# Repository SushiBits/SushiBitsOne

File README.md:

# SushiBits One

ARM Cortex-M in Arduino form factor, and consumes very little power.

## Introduction & Goal

This is one of my "design challenges" to myself:

*   Arduino-compatible form factor,
*   Take an 48-pin STM32 microcontroller (since STM32F103CBT6 are that cheap,)
*   Bring all I/O pins out somewhere, be it the connectors, JTAG or USB,
*   No two pins can be shorted together,
*   Use only switch-mode power supply,
*   Two layer PCB only,
*   Single side load.

## Main components

*   STM32 microcontroller in LQFP-48 package. I have tested the following:
    *   STM32F072C8T6 (Cortex-M0 @48MHz)
    *   STM32F103CBT6 (Cortex-M3 @72MHz)
    *   STM32L151CCT6 (Cortex-M3 @32MHz, ULP)
    *   STM32F303CCT6 (Cortex-M4F @72MHz)
    *   STM32F373CCT6 (Cortex-M4F @72MHz)
*   WCH CH340B: USB to UART adapter.
*   TI TPS562200: VIN to 5V buck converter.
*   TI LM3671-3.3: 5V to 3.3V buck converter.

## License

This is [open source hardware](http://www.oshwa.org/), licensed under the
[3-clause BSD license](LICENSE.md).

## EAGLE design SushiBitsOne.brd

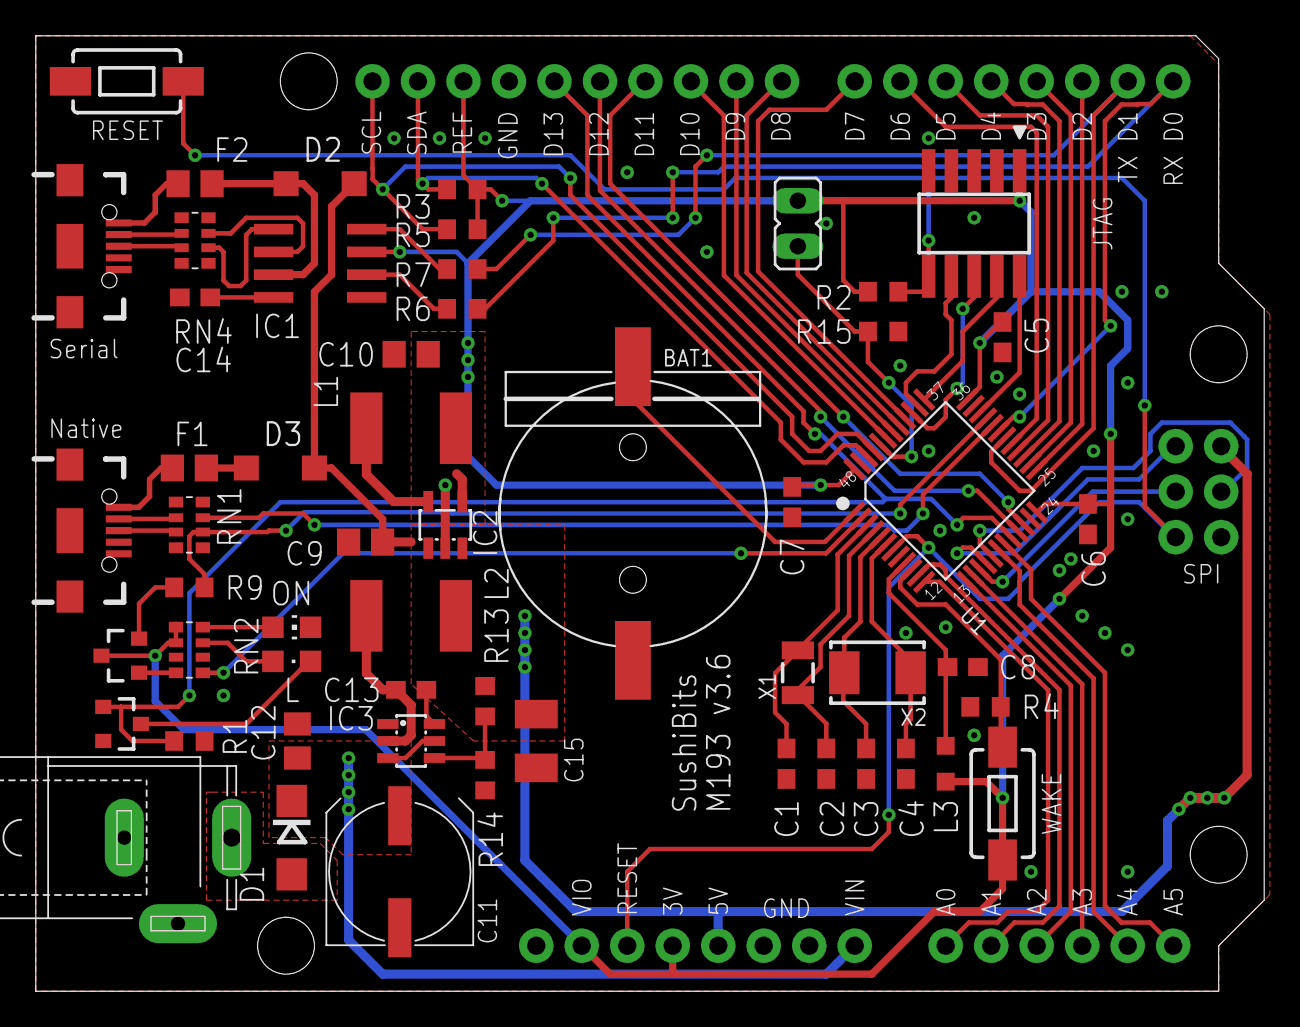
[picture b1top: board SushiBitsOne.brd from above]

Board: 2 copper layers, 68.6 x 53.3 mm, 56 parts (0 on the bottom side), 68 nets.

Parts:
BAT1: CR1220; BAT2P-SMD-16.4-CR1220
C1, C2: 3p; C0603
C3, C4: 22p; C0603
C5, C6, C7, C8, C13: 100n; C0603
C9, C10, C12: 10u; C0805
C11: 100u; UD-8X10_NICHICON
C14: 1u; C0603
C15: 220u; SMC_B
D1: SS34; DO214AC
D2, D3: SS14; SOD123
F1, F2: 500mA; R0805
IC1: HT42B534; SO8
IC2: LM3671-3.3DBV; SOT23-5L
IC3: TPS562200DBV; SOT23-6L
J1: ARDUINO_R3
J2: SPC4077
J3, J4: USB-B-MICRO-SMD
JP1: BOOT; JP1
L1: 2.2u; L5650M
L2: 4.7u; L5650M
L3: L2012C
LED1: Amber; CHIPLED_0805
LED2: Green; CHIP-LED0805
Q1: 2N7002; SOT23-3
Q2: MMBT2222A; SOT23-3
R1, R2, R4: 10k; R0603
R3, R5, R15: 4.7k; R0603
R6, R7: 510; R0603
R9: 1.5k; R0603
R13: 11k; R0603
R14: 2k; R0603
RN1, RN4: 22; EXB38V
RN2: 510; EXB38V
S1: RESET; TACTILE-SWITCH-1101NE
S2: WKUP; TACTILE-SWITCH-1101NE
U1: STM32F103CBT6-LQFP48; LQFP48-0.5-7X7MM
X1: 32768Hz; CRYSTAL-SMD-3.2X1.5MM
X2: 8MHz; CRYSTAL-SMD-5X3.2-2PAD
X3: JTAG; 1365-10

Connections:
+3V3: C5.1, C6.1, C7.1, C10.1, IC1.3, IC2.4, J1.3.3V, J1.AREF, J1.IOREF, JP1.1, L1.1, L3.1, Q2.3, R2.2, R3.2, R5.2, RN2.1, RN2.2, S2.2, U1.24, U1.36, U1.48, X3.1
+5V: C9.1, C15.+, D2.C, D3.C, IC2.1, IC2.3, J1.5V, J1.VCC, L2.1, R13.2
A0: J1.A0, U1.12
A1: J1.A1, U1.11
A2: J1.A2, U1.13
A3: J1.A3, U1.14
A4: J1.A4, U1.18
A5: J1.A5, U1.19
D2: J1.D2, U1.25
D3: J1.D3, U1.26
D4: J1.D4, U1.27
D5: J1.D5, U1.28
D6: J1.D6, U1.29
D7: J1.D7, U1.40
D8: J1.D8, U1.41
D9: J1.D9, U1.42
D10: J1.D10, U1.43
D11: J1.D11, U1.22
D12: J1.D12, U1.21
D13: J1.D13, Q1.1, R1.2, U1.20
D14: RN2.5, U1.2
GND: BAT1.-, C1.2, C2.2, C3.2, C4.2, C5.2, C6.2, C7.2, C8.2, C9.2, C10.2, C11.-, C12.2, C14.2, C15.-, IC1.1, IC2.2, IC3.1, J1.GND@1, J1.GND@2, J1.GND@3, J1.GND@4, J2.1, J2.2, J3.GND, J3.SHIELD1, J3.SHIELD2, J3.SHIELD3, J4.GND, J4.SHIELD1, J4.SHIELD2, J4.SHIELD3, LED2.C, Q1.2, R1.1, R4.1, R14.1, R15.1, S1.1, U1.8, U1.23, U1.35, U1.47, X3.3, X3.5, X3.9
HSEIN: C3.1, U1.5, X2.P$1
HSEOUT: C4.1, U1.6, X2.P$2
JTCK: U1.37, X3.4
JTDI: U1.38, X3.8
JTDO: U1.39, X3.6
JTMS: U1.34, X3.2
LSEIN: C1.1, U1.3, X1.P$1
LSEOUT: C2.1, U1.4, X1.P$2
MISO: J1.MISO, U1.16
MOSI: J1.MOSI, U1.17
unnamed: J4.D-, RN1.2
unnamed: J4.D+, RN1.3
unnamed: IC1.6, RN4.7
unnamed: IC1.5, RN4.6
unnamed: IC1.2, R6.1
unnamed: IC1.4, R7.1
unnamed: LED2.A, RN2.8
unnamed: LED1.C, Q1.3
unnamed: LED1.A, RN2.7
unnamed: IC2.5, L1.2
unnamed: D1.A, J2.3
unnamed: JP1.2, R15.2, U1.44
unnamed: D3.A, F1.2
unnamed: C13.1, IC3.2, L2.2
unnamed: C13.2, IC3.6
unnamed: D2.A, F2.2, IC1.7
unnamed: IC3.4, R13.1, R14.2
unnamed: Q2.2, R9.2
unnamed: Q2.1, RN2.4
unnamed: C8.1, L3.2, U1.9
unnamed: C14.1, IC1.8
unnamed: J3.D+, RN4.3
unnamed: J3.D-, RN4.2
unnamed: F2.1, J3.VBUS
RESET#: J1.RESET@1, J1.RESET@2, R2.1, S1.2, U1.7, X3.10
RXD: J1.D0, R6.2, U1.31
SCK: J1.SCK, U1.15
SCL: J1.SCL, R5.1, U1.45
SDA: J1.SDA, R3.1, U1.46
TXD: J1.D1, R7.2, U1.30
UD+: R9.1, RN1.6, U1.33
UD-: RN1.7, U1.32
VBAT: BAT1.+, U1.1
VBUS2: F1.1, J4.VBUS
VIN: C11.+, C12.1, D1.C, IC3.3, IC3.5, J1.VIN
WKUP: R4.2, S2.1, U1.10

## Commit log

2017-03-23 Initial Commit for completed project
2017-03-23 The ignore file missed the *.mil
2017-03-23 Added a README
2017-03-26 Fixing a typo in README
2017-08-19 Release: M193v3
2017-08-20 Updated copyright text in LICENSE
2017-11-02 Adjusting for the v4
2017-11-02 Ignoring a few EAGLE files
2017-11-02 Ignoring even more EAGLE files
2017-11-02 Implemented the USB microcontroller with USB-Serial and CMSIS-DAP.
2017-11-02 Ignoring release files
2017-11-02 Releasing M193v4
2017-11-02 Preparing v3.1 release.
2017-11-02 Missed a spot check on board silkscreen
2017-11-03 There is a net overlap.
2017-12-04 Relayout the board to accomodate component changes.
2017-12-04 Change up some footprints.
2017-12-20 Some manufacturability and cleanup work
2017-12-20 Squeezed the onboard debugger back in.
2017-12-20 Some details of the files are somehow changed?
2017-12-20 Adding the pin indicator back on DAP42
2017-12-21 One track is cut off by the hole...
2017-12-21 I missed the version number on the PDF file

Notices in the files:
parts and their libraries:
SparkFun-Boards: Licensing: Creative Commons ShareAlike 4.0 International - https://creativecommons.org/licenses/by-sa/4.0
